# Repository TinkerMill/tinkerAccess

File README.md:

# tinkerAccess
The tinkerAccess system is a Raspberry Pi based access control system that can be used to prevent unauthorized users from using devices that require special training. It could also conceivably be used to control electronic lock boxes or doors.

The system was originally designed and created by Matt Stallard, Ron Thomas, and Matt Peopping for TinkerMill a makerspace in Longmont, CO. It is continually being maintained and enhanced by other contributors in the community.

### Install the tinkerAccess system

There are two main components to the system. If you intend to use the client and server software on separate physical devices, then you will want to review the individual documents regarding the installation, configuration, and operation of each respective piece.

- [tinker-access-server](/tinker_access_server/README.md) 
- [tinker-access-client](/tinker_access_client/README.md)

If however, you intend to use both the server and client on the same physical device, then you can follow these simple instructions. You will need to complete these client [prerequisites](/tinker_access_client/docs/prerequisites.md) before running the install script. 

From the Pi terminal:

```
git clone https://github.com/TinkerMill/tinkerAccess.git
cd tinkerAccess
sudo bash install.sh
```

After running the installation script, the configuration files for both the server and client are created, but they need to be modified for a proper setup, before rebooting or restarting the services to take effect.

Edit the server configuration file:

```
sudo nano /opt/tinkeraccess/server.cfg
```

Edit the client configuration file:

```
sudo nano /etc/tinker-access-client.conf
```

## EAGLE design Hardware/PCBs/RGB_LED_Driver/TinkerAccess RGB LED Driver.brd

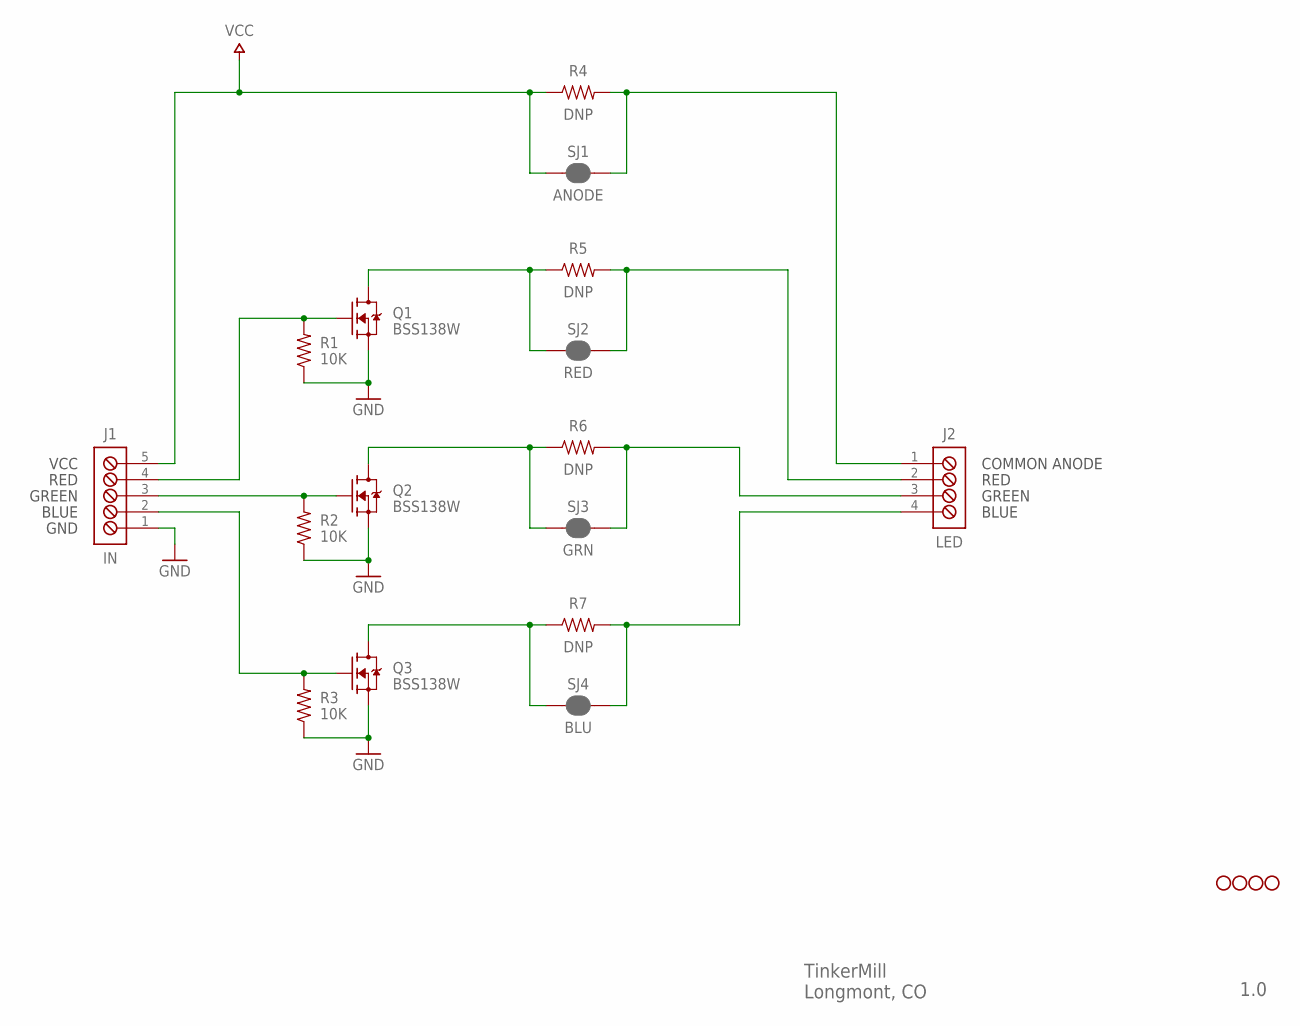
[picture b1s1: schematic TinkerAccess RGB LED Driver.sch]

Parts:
J1: IN; ON_SHORE_OSTVN05A150
J2: LED; ON_SHORE_OSTVN04A150
Q1, Q2, Q3: BSS138W; SOT323
R1, R2, R3: 10K; 0603
R4, R5, R6, R7: DNP; 0603
SJ1: ANODE; JMP_PAD_2X1_CLOSED_BY_PASTE
SJ2: RED; JMP_PAD_2X1_CLOSED_BY_PASTE
SJ3: GRN; JMP_PAD_2X1_CLOSED_BY_PASTE
SJ4: BLU; JMP_PAD_2X1_CLOSED_BY_PASTE
STANDOFF1, STANDOFF2, STANDOFF3, STANDOFF4: STANDOFF_2.3MM_NO_CU

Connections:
GND: J1.1, Q1.2 (S), Q2.2 (S), Q3.2 (S), R1.1, R2.1, R3.1
unnamed: J1.4, Q1.1 (G), R1.2
unnamed: J1.3, Q2.1 (G), R2.2
unnamed: J1.2, Q3.1 (G), R3.2
unnamed: J2.2, R5.2, SJ2.2
unnamed: J2.3, R6.2, SJ3.2
unnamed: J2.4, R7.2, SJ4.2
unnamed: Q1.3 (D), R5.1, SJ2.1
unnamed: Q2.3 (D), R6.1, SJ3.1
unnamed: Q3.3 (D), R7.1, SJ4.1
unnamed: J2.1, R4.2, SJ1.2
VCC: J1.5, R4.1, SJ1.1

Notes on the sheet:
VCC
RED
GREEN
BLUE
GND
COMMON ANODE
TinkerMill Longmont, CO
1.0

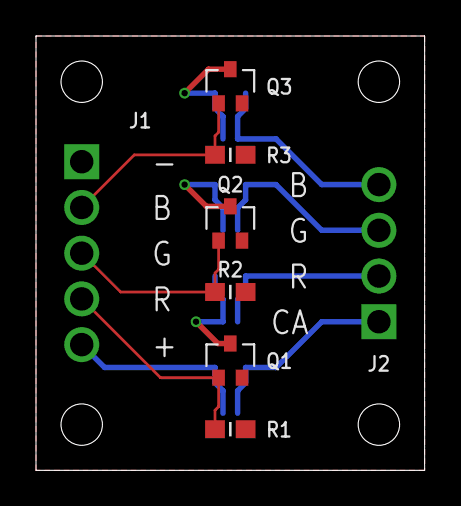
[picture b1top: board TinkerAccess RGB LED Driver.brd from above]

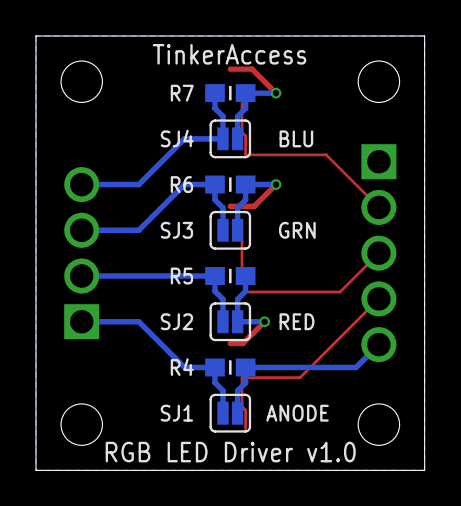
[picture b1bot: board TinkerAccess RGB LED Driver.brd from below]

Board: 2 copper layers, 21.6 x 24.1 mm, 20 parts (8 on the bottom side), 12 nets.

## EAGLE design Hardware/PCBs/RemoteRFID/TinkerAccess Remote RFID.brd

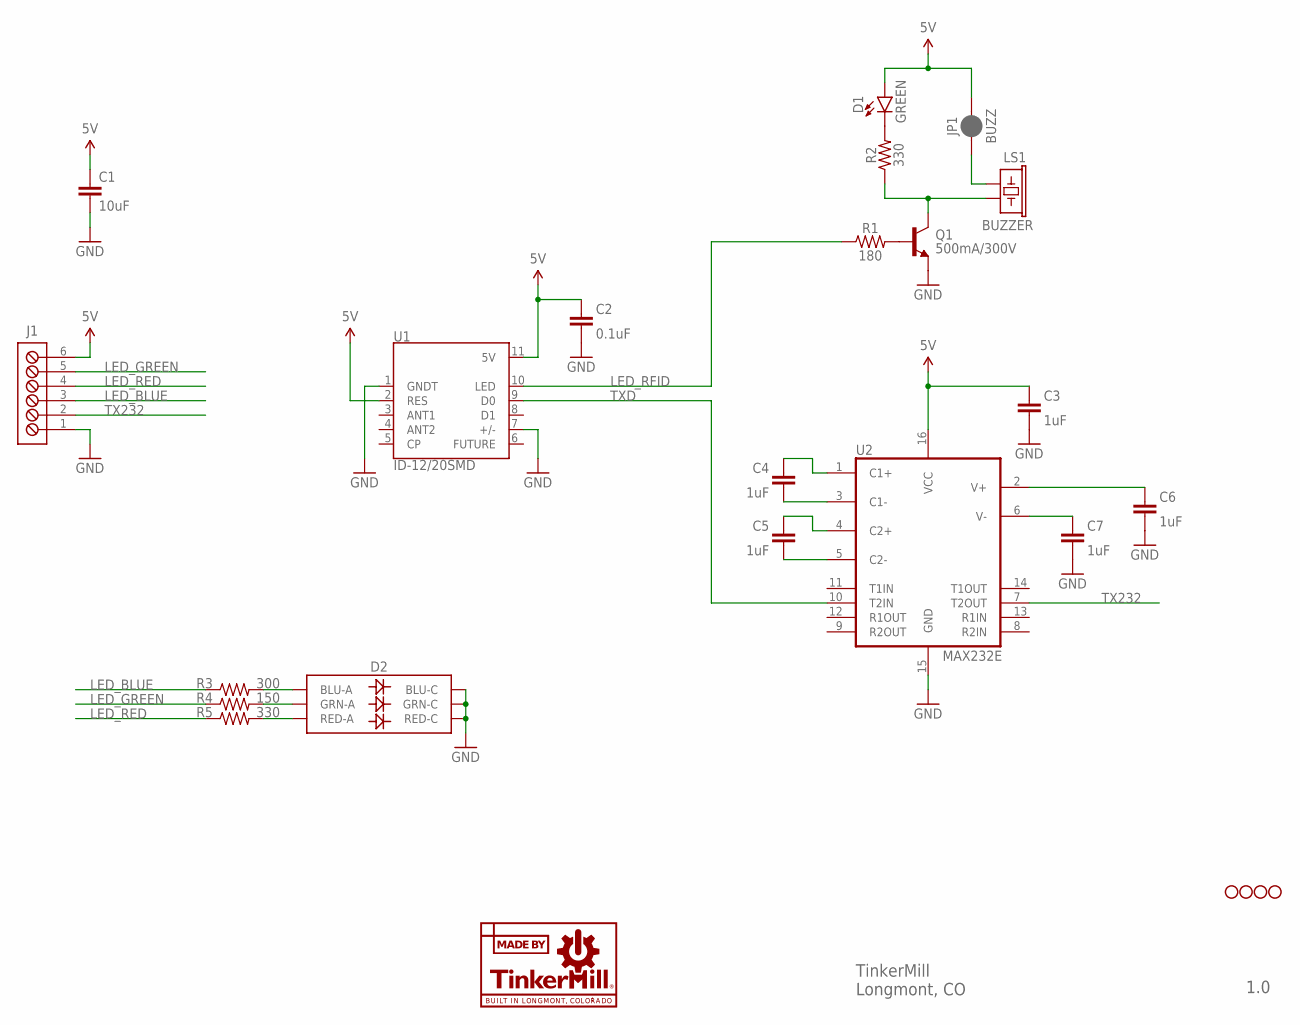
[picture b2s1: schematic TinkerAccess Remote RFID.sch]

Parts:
C1: 10uF; 1206
C2: 0.1uF; 0603
C3, C4, C5, C6, C7: 1uF; 0603
D1: GREEN; LED-1206
D2: LED-RGBNO_IC; LED-TRICOLOR-5050
J1: TB_6X1_TE_CONN_ED555_6DS; TE_CONN_ED555_6DS
JP1: BUZZ; SMT-JUMPER_2_NC_PASTE_NO-SILK
LOGO1: MADE_BY_TINKERMILL
LS1: BUZZER; BUZZER-CCV
Q1: 500mA/300V; SOT23-3
R1: 180; 0603
R2, R5: 330; 0603
R3: 300; 0603
R4: 150; 0603
STANDOFF1, STANDOFF2, STANDOFF3, STANDOFF4: STANDOFF_3.2MM_NO_CU_MASK
U1: ID-12/20SMD; ID-12_SMD
U2: MAX232E; TSSOP16

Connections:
5V: C1.1, C2.2, C3.2, D1.A, J1.6, JP1.2, U1.2 (RES), U1.11 (5V), U2.16 (VCC)
GND: C1.2, C2.1, C3.1, C6.1, C7.1, D2.4 (BLU-C), D2.5 (RED-C), D2.6 (GRN-C), J1.1, Q1.2 (E), U1.1 (GNDT), U1.7 (+/-), U2.15 (GND)
LED_BLUE: J1.3, R3.1
LED_GREEN: J1.5, R4.1
LED_RED: J1.4, R5.1
LED_RFID: R1.1, U1.10 (LED)
unnamed: Q1.1 (B), R1.2
unnamed: JP1.1, LS1.+ (1)
unnamed: LS1.- (2), Q1.3 (C), R2.1
unnamed: D1.C, R2.2
unnamed: C4.1, U2.3 (C1-)
unnamed: C4.2, U2.1 (C1+)
unnamed: C5.1, U2.5 (C2-)
unnamed: C5.2, U2.4 (C2+)
unnamed: D2.2 (RED-A), R5.2
unnamed: D2.1 (GRN-A), R4.2
unnamed: D2.3 (BLU-A), R3.2
unnamed: C6.2, U2.2 (V+)
unnamed: C7.2, U2.6 (V-)
TX232: J1.2, U2.7 (T2OUT)
TXD: U1.9 (D0), U2.10 (T2IN)

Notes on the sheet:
TinkerMill Longmont, CO
1.0

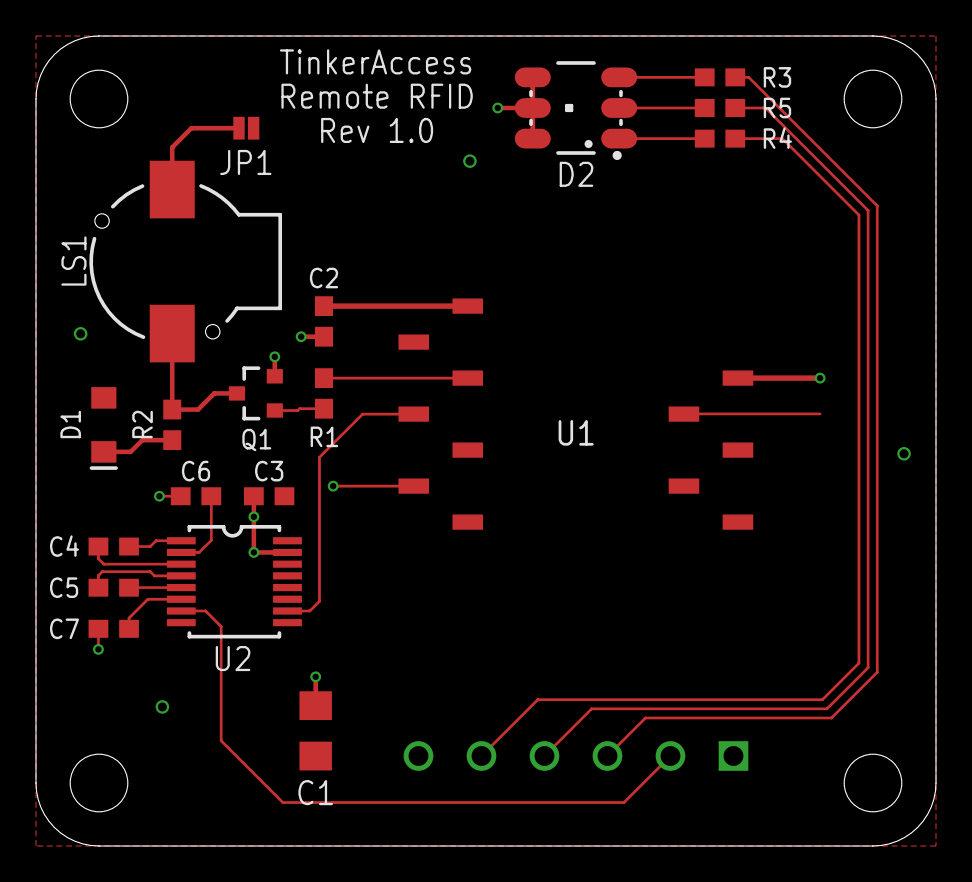
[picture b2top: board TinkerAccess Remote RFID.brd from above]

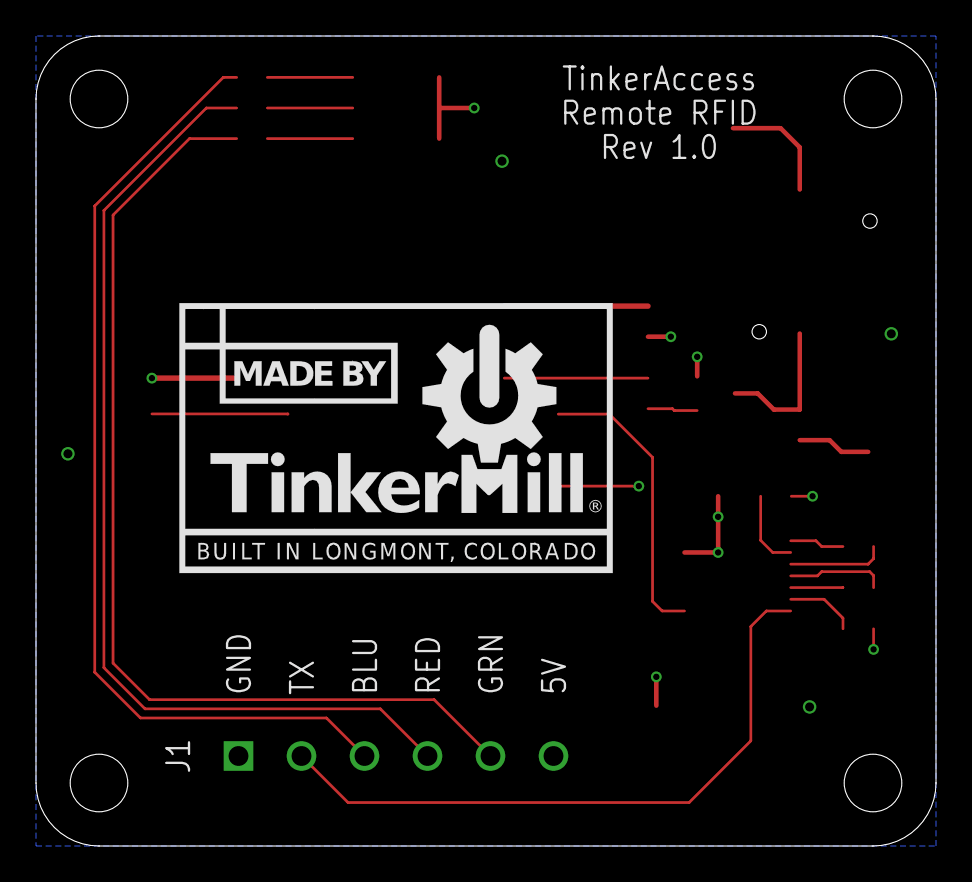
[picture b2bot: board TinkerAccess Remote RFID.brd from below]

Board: 2 copper layers, 50.0 x 45.0 mm, 25 parts (2 on the bottom side), 21 nets.

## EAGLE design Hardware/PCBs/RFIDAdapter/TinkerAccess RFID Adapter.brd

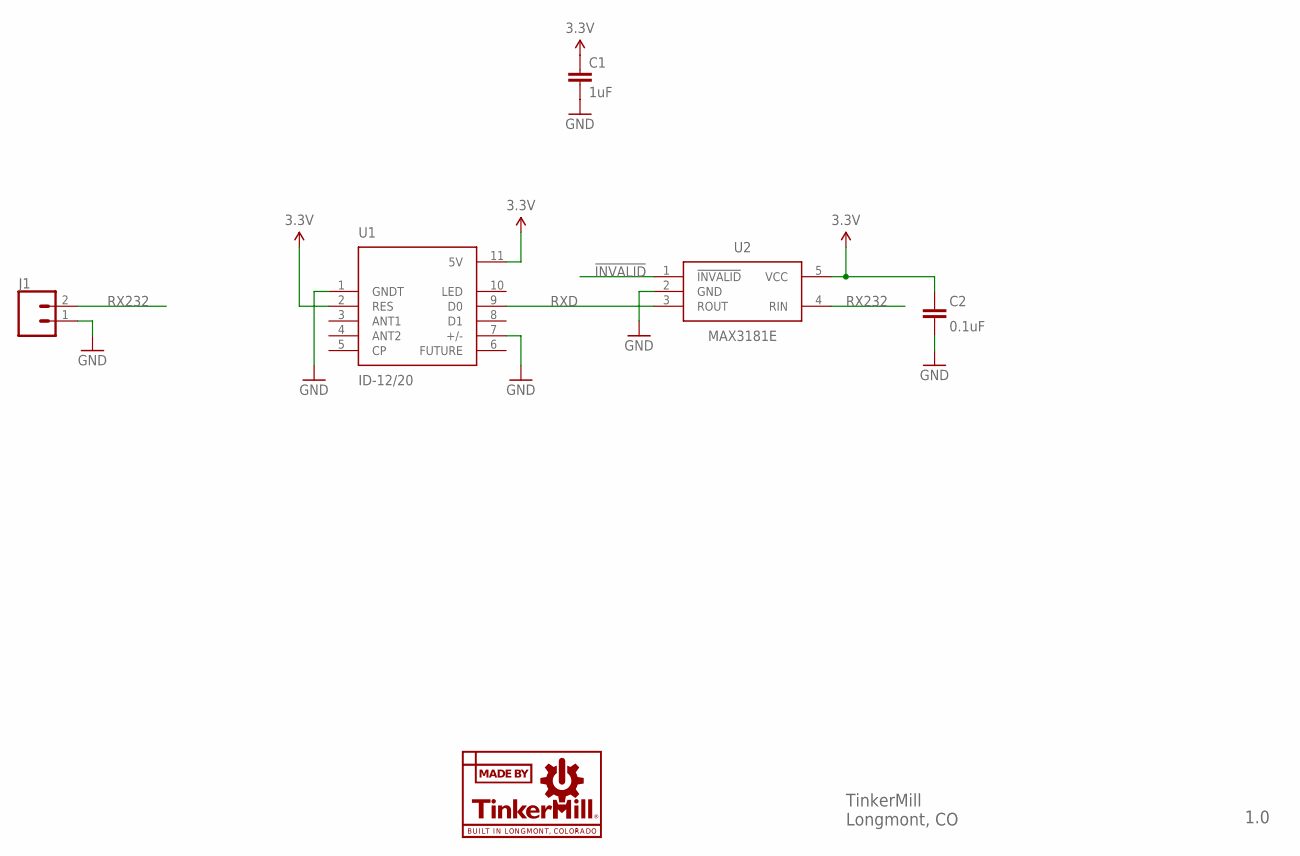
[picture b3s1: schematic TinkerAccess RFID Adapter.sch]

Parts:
C1: 1uF; 0603
C2: 0.1uF; 0603
J1: CONN_025MM; SCREWTERMINAL-5MM-2
LOGO1: MADE_BY_TINKERMILL
U1: ID-12/20; ID-12
U2: MAX3181E; SOT23-5

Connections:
3.3V: C1.1, C2.2, U1.2 (RES), U1.11 (5V), U2.5 (VCC)
!INVALID: U2.1 (!INVALID)
GND: C1.2, C2.1, J1.1, U1.1 (GNDT), U1.7 (+/-), U2.2 (GND)
RX232: J1.2, U2.4 (RIN)
RXD: U1.9 (D0), U2.3 (ROUT)

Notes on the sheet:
TinkerMill Longmont, CO
1.0

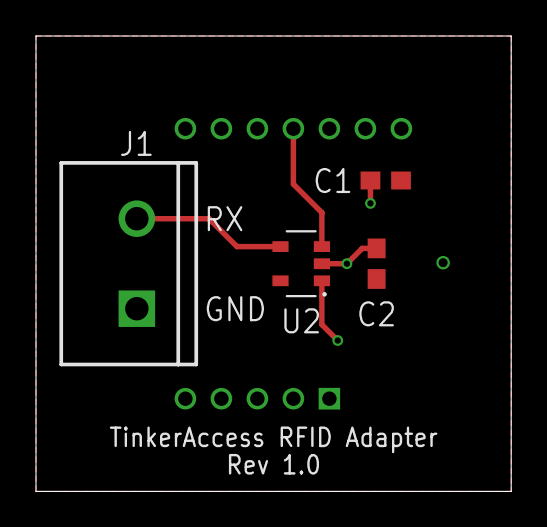
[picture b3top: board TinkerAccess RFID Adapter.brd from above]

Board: 2 copper layers, 26.4 x 25.3 mm, 6 parts (1 on the bottom side), 4 nets.

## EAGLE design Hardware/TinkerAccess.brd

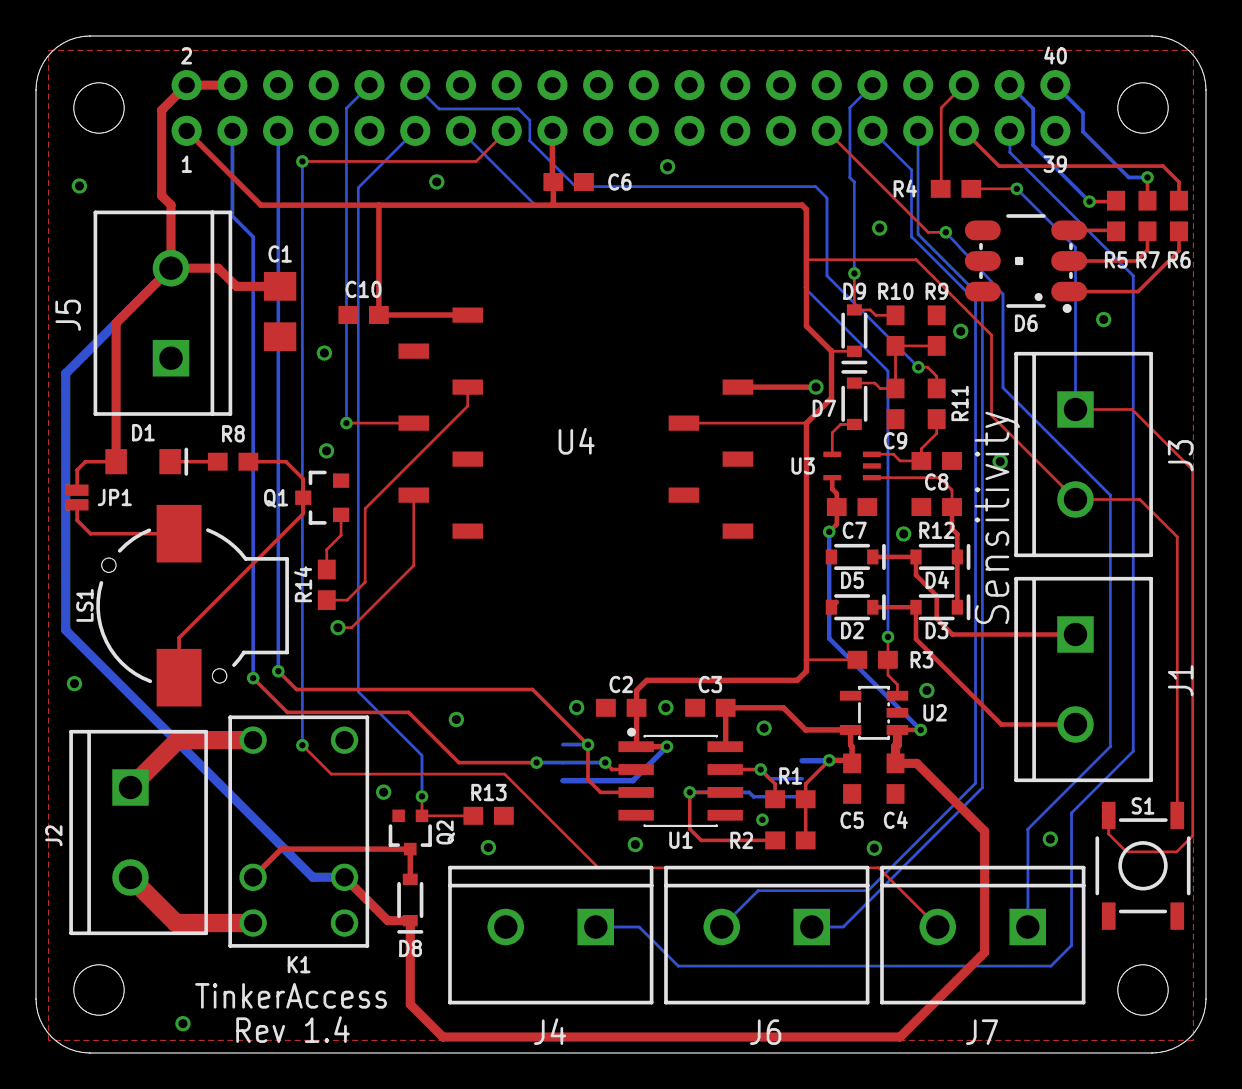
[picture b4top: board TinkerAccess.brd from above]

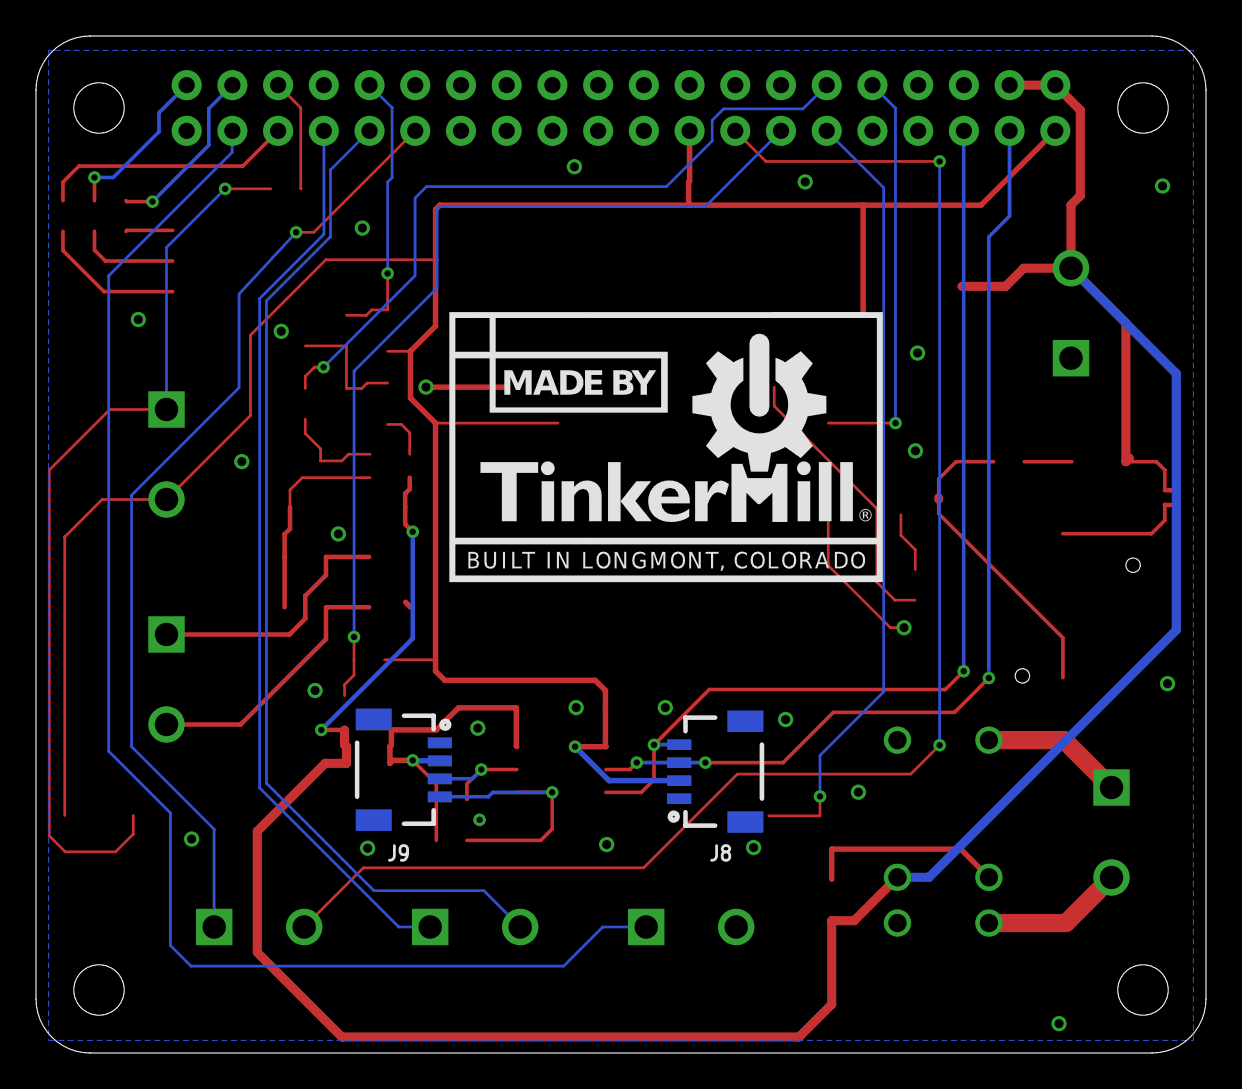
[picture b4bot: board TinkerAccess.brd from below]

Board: 2 copper layers, 65.0 x 56.5 mm, 54 parts (3 on the bottom side), 40 nets.

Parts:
C1: 10uF; 1206
C2, C3, C7, C10: 0.1uF; 0603
C4, C5, C6, C8, C9: 1uF; 0603
D1: GREEN; LED-1206
D2, D3, D4, D5, D7, D8, D9: 1A/100V; SOD-323
D6: LED-TRICOLOR-5050
J1, J2, J3, J4, J5, J6, J7: SCREWTERMINAL-5MM-2
J8, J9: 1X04_1MM_RA
JP1: BUZZ; SMT-JUMPER_2_NC_PASTE_NO-SILK
K1: RELAY-SPDT-2-G5V; RELAY-G5V
LOGO1: MADE_BY_TINKERMILL
LS1: BUZZER; BUZZER-CCV
Q1: 500mA/300V; SOT23-3
Q2: 310mA/60V/1.6Ω; SOT323
R1, R2, R3, R4, R11, R13: 10k; 0603
R5: 300; 0603
R6: 150; 0603
R7, R8: 330; 0603
R9: 100k; 0603
R10, R12: 1k; 0603
R14: 180; 0603
RPI1: RASPBERRYPI_BPLUS_HATNOSLOTS; PI_HAT_NOSLOTS
S1: LogOut; TACTILE_SWITCH_SMD_5.2MM
U1: Si8600AC; SOIC127P600X175-8
U2: AP2112; SOT23-5
U3: ADCMP-371; SC-70-5
U4: ID-12/20SMD; ID-12_SMD

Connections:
3.3V: C2.2, C6.1, C10.2, D9.C, J3.2, J8.2, R3.1, RPI1.1, RPI1.17, S1.1, U1.1, U4.2, U4.11
3.3V_EN: R3.2, RPI1.13, U2.3
5V: C1.1, C4.1, C7.1, D1.A, D8.C, J5.2, JP1.2, K1.2, RPI1.2, RPI1.4, U2.1, U3.5
+3V3: C3.2, C5.1, J9.2, R1.1, R2.1, U1.8, U2.5
AC1: D4.A, D5.C, J1.1
AC2: D2.C, D3.A, J1.2
BSCL: J9.4, R2.2, U1.6
BSDA: J9.3, R1.2, U1.7
COMPOUT: D7.A, U3.4
DETECT: C9.1, D7.C, R9.1, R10.1
GND: C1.2, C2.1, C3.1, C4.2, C5.2, C6.2, C7.2, C8.2, C9.2, C10.1, D2.A, D5.A, D6.4, D6.5, D6.6, J4.2, J5.1, J8.1, J9.1, Q1.2, Q2.2, R9.2, R12.1, R13.2, RPI1.6, RPI1.9, RPI1.14, RPI1.20, RPI1.25, RPI1.30, RPI1.34, RPI1.39, U1.4, U1.5, U2.2, U3.2, U4.1, U4.7
GPIO5: J7.1, RPI1.29
GPIO6: J6.2, RPI1.31
GPIO12: D9.A, R10.2, RPI1.32
GPIO13: J6.1, RPI1.33
GPIO16: R4.2, RPI1.36
GPIO18: R11.1, RPI1.12
GPIO22: J7.2, RPI1.15
GPIO26: J4.1, RPI1.37
LED_BLUE: R5.1, RPI1.38
LED_GREEN: R6.1, RPI1.35
LED_RED: R7.1, RPI1.40
LED_RFID: R14.1, U4.10
LOGOUT: J3.1, R4.1, S1.3
unnamed: Q1.1, R14.2
unnamed: JP1.1, LS1.+
unnamed: LS1.-, Q1.3, R8.1
unnamed: D1.C, R8.2
unnamed: D8.A, K1.9, Q2.3
unnamed: J2.1, K1.6
unnamed: J2.2, K1.10
unnamed: D6.2, R7.2
unnamed: D6.1, R6.2
unnamed: D6.3, R5.2
RECT+: D3.C, D4.C, R12.2, U3.1
RELAY: Q2.1, R13.1, RPI1.11
RXD: RPI1.10, U4.9
SCL: J8.4, RPI1.5, U1.3
SDA: J8.3, RPI1.3, U1.2
VREF: C8.1, R11.2, U3.3

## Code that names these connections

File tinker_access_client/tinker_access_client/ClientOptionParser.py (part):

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ClientOptionDefaults = {
    ClientOption.DEBUG: False,
    ClientOption.LOG_LEVEL: 40,
    ClientOption.PIN_LOGOUT: 16,
    ClientOption.PIN_LED_RED: 21,
    ClientOption.DEVICE_ID: None,
    ClientOption.PIN_LED_BLUE: 20,
    ClientOption.REBOOT_DELAY: 300,
    ClientOption.PIN_LED_GREEN: 19,
    ClientOption.AUTO_UPDATE: False,
    ClientOption.FORCE_UPDATE: False,
    ClientOption.PIN_POWER_RELAY: 17,
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        )

        self.__parser.add_option(
            '--pin-logout',
            help='the logout pin [default:%default]',
            default=ClientOptionDefaults[ClientOption.PIN_LOGOUT],
            dest=ClientOption.PIN_LOGOUT,
            type='int',
            action='store'
        )

        self.__parser.add_option(
            '--pin-power-relay',
            help='the power relay pin [default:%default]',
            default=ClientOptionDefaults[ClientOption.PIN_POWER_RELAY],
            dest=ClientOption.PIN_POWER_RELAY,
            type='int',
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        self.__parser.add_option(
            '--pin-led-red',
            help='the red led pin [default:%default]',
            default=ClientOptionDefaults[ClientOption.PIN_LED_RED],
            dest=ClientOption.PIN_LED_RED,
            type='int',
            action='store'
        )
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        self.__parser.add_option(
            '--pin-led-green',
            help='the green led pin [default:%default]',
            default=ClientOptionDefaults[ClientOption.PIN_LED_GREEN],
            dest=ClientOption.PIN_LED_GREEN,
            type='int',
            action='store'
        )
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        self.__parser.add_option(
            '--pin-led-blue',
            help='the blue led pin [default:%default]',
            default=ClientOptionDefaults[ClientOption.PIN_LED_BLUE],
            dest=ClientOption.PIN_LED_BLUE,
            type='int',
            action='store'
        )
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        )

        self.__parser.add_option(
            '--pin-bypass-detect',
            help='the bypass detect pin [default:%default]',
            default=ClientOptionDefaults[ClientOption.PIN_BYPASS_DETECT],
            dest=ClientOption.PIN_BYPASS_DETECT,
            type='int',
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
        self.__parser.add_option(
            '--use-estop',
            help='use the e-stop pin to detect an e-stop event [default:%default]',
            default=ClientOptionDefaults[ClientOption.USE_ESTOP],
            dest=ClientOption.USE_ESTOP,
            action='store_true'
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
        self.__parser.add_option(
            '--use-bypass-detect',
            help='use the bypass detect pin function [default:\'%default\']',
            default=ClientOptionDefaults[ClientOption.USE_BYPASS_DETECT],
            dest=ClientOption.USE_BYPASS_DETECT,
            action='store_true'
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
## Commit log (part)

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2015-07-12 initial scanner
2015-08-16 dd ser
2015-09-02 more html changes
2015-09-02 adding ignore file
2015-09-23 inst
2015-09-30 New user table and web interface to use it
2015-10-29 fix testing instruction
2015-10-29 Mostly working server code, you can add and remove access for users
2015-10-29 updated docs
2015-10-29 fix servername
2015-10-29 fix formatting
2015-10-30 install script and startup scripts
2015-10-30 fixing installer
2015-10-30 point to database
2015-10-30 working
2015-10-31 add python deps to installer
2015-11-04 initial checkin
2015-11-04 Changed return value in memberAccessServer.py. We actually will not need this memberAccessServer.py file. It was only used during early development testing to confirm flask was working correctly.
2015-11-05 don't add to new users over and over, only add if they are not in new users and if they are not in users
2015-11-13 Adding Secutiry somewhat
2015-11-18 Corrected issue involved with invalid user scanning while a valid user is logged in.
2015-11-18 changes for lcd 0x06 to 0x0C
2015-11-18 update docs
2015-11-18 full path in install
2015-11-18 updated startup script for tinkerclient
2015-11-19 bug deleting wrong user
2015-11-19 move sql up
2015-11-19 redirect to login if you are not logged in
2015-11-19 change perms 755 badge scan
2016-01-21 test2
    testing webhook2
2016-01-23 push to slack
2016-01-23 add user to message
2016-01-23 simple test script
2016-01-23 added LED status
2016-01-23 fix template error
2016-01-23 fixing template for log
2016-01-27 client files into oldcode
2016-01-30 mostly working
2016-01-31 logging?
2016-01-31 cleanup file names
2016-01-31 device manager added back
2016-01-31 python header
2016-01-31 make image smaller
2016-02-12 gave server static ip
2016-02-12 removed old instructions.
2016-02-28 Fixed pin_current_sense technology
2016-02-28 move led function up
2016-02-29 more verbose go the F away message
2016-02-29 2 f'in seconds... happy matt?
2016-03-04 Added coast-down delay functionality
    If a logout request happens while the machine is running, this added
    functionality ensures that the logout event doesn't execute until a
    coast-down period elapses.
2016-03-06 changed load resistor value
2016-03-07 RFID diagram - Unscrewing the screw up
2016-03-07 Created docs folder
2016-03-13 This closes #3, and closes #4
2016-03-13 more errors
2016-03-13 fix typo
2016-03-13 time input wrong.corrected
2016-03-13 Verbose output on machine down, and global for currentBadge
2016-03-13 startup script installs new client
2016-04-15 remove continue
2016-04-20 fixing matts vars
2016-05-09 updated docs and install script
2016-05-11 adding run.cfg back
2016-05-11 updated true=0 false=1 for those that are overly anal about their trues and falses
2016-05-11 Mario mode added to client, hold down logout for 2 seconds to activate click logout again to logout
2016-05-13 remove server debug line
2016-05-15 lowered count cycle on reset button hold down
    went from 2000 to 20 since there is a .1 sleep cycle each time it loops... so I only have to hold down for 2 second instead of 200 :)
2016-05-16 Update client.py
    fixy fixy
2016-05-16 more error checking
2016-05-16 keep mario message up, continue if can't talk to server
2016-05-16 option to force an update from script
2016-05-16 place abs path back into server config for db
2016-05-17 lalalalal
2016-05-17 log to syslog on client
2016-05-20 Capture entire 12-character RFID badge number.
2016-05-26 clean old records on new user
2016-05-26 flush serial after reading data
2016-05-26 read 12 prev chars
2016-05-27 lalala server fix
2016-05-28 Corrected Service Management Instructions
2016-05-31 Upload CSV option on server
2016-07-06 Uploaded RFIDTagRegster.py.
    RFIDTagRegister.py is a script that reads in an RFID tag number using the Sparkfun RFID reader and auto-types the tag number.
2016-11-02 Updated circuit schematics
    Improved current sense circuit and corrected LED resistor values.
2016-11-09 Fixed typo and clarified variables
2016-11-09 Missed a tab/space... Oops!
2016-11-09 Use modulo for minutes remaining.
2016-11-12 Fixed arithmetic to display h:m:s on LCD
2016-11-12 h:m:s arithmetic correction number 2, I swear I know math...
2016-11-12 Importing math
2016-11-13 Added 2 second timeout for server requests
2016-11-13 Added 2 second delay after error logging in message display
2016-11-23 Increased server response timeout to five seconds.
2016-11-29 Refactor to add logging for all client request
2016-11-30 Revert "Removed code that would cause duplicate log messages"
    This reverts commit 1f643b83fb6d0a186454d6c3408f051573ecaa93.
2016-12-22 Increased timeout to 10 seconds.
2017-03-17 Set build VERSION number
2017-04-02 (issue): #11 - Current Sense/Coastdown Time not implemented correctly
2017-05-09 Convert LCD from GPIO to I2C.
2017-05-11 Change smbus to smbus2, add smbus2 to setup.py
2017-05-11 Remove .GPIO from __write_to_lcd
2017-05-11 Update DeviceApi to match LcdApi
2017-05-11 Update VirtualDevice in integration test utils to match DeviceApi
2017-05-12 Add 0 to write_byte_data invocation.
2017-05-12 Remove __write_to_lcd from VirtualDevice.py
2017-05-13 Break i2c_device class into its own file
2017-05-18 Add fritzing file and exported images
2017-05-18 Update client prerequisite documentation
2017-07-12 Add new Fritzing file for Raspberry Pi Hat design
2017-07-12 Add Hat board exports
2017-07-18 Add power to U2 LM393 thanks to Tyler
2017-07-19 Fix issues found by Tyler Dow and Don Vukovic
2017-07-19 Update exported Bill of Materials and Netlists
2017-07-19 Update exported PCB files
2019-04-09 Update Client.py
    We are opening the file but never closing it. Should always close a file when done with it...
2019-06-26 basic tool summary page
2019-08-27 tool summary updates
2019-12-19 Create TinkerAccess.brd
    Version V1_2 from Don Vukovic
2019-12-20 Create LICENSE
2020-02-18 Fixed Consistancy Errors
    After fixing consistancy errors I now need to make the repairs to the pad designs.
2020-02-20 Finshied Removing HW bugs
    Fixed missing trace, Pad sizes for ADCMP371 and SI8600. Also added a trace for the 3.3V en to a GPIO for restarting the
2020-02-23 bugfix to get correct PID to kill on shutdown
    Running `/opt/tinkeraccess/server.py` directly saves the wrong PID in
    `/var/run/tinkerAccessServer.pid`, which is later used to kill the
    server when the service is stopped. Instead, running the server via
    `python /opt/tinkeraccess/server.py` reports the correct PID.
2020-02-26 Added --noreload option to server
    Prevents zombie server when run from /etc/init.d/tinkerserver. The Flask
    server by default runs a child process, which is the actual webserver,
    so that the parent can monitor the server files and restart the child
    when they change. This, however, interferes with start-stop-daemon's
    ability to stop the server. This change fixes that behavior.
2020-05-23 TinkerBoard Update
    Fixed Drill Hole size to match Design rules.
    Fixed Pad sizes.
    Fixed AirWires.
2020-05-24 added pulldown
    Added pulldown resistor to 3v3 Enable line
2020-05-29 Cleaned up schematic notes
2020-06-19 Updates to machine shop TA schematic.
2020-06-20 ran 2to3
2020-06-27 Added support for new SparkFun LCD-14072 SerLCD display Added support for an E-STOP input pin to detect an event and automatically logout the current user Added support for the 3.3V enable pin added 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
2020-06-27 Moved E-Stop input to GPIO6 Added machine shop faceplate DXF file
2020-06-27 Fixed test assertions for training mode
2020-06-28 Added example client config file
2020-07-07 Added a bypass/tamper detect input
2020-07-14 Updated machine shop schematic with bypass detect changes
2020-08-05 prototype of image capture/posting
2020-08-06 moved server.cfg to example_server.cfg
2020-08-14 Cleaned up the tests so that they will pass with recent code changes
2020-08-14 Added alarm beacon wiring to machine shop TinkerAccess schematic
2020-08-14 fixes to run without webcam
2020-08-19 Documentation and install script updates for the client.
2020-08-20 Changes for PCB spin with a PWM based current sense detect setting
2020-08-20 Documentation updates for programmable current detection tuning
2020-08-20 Fix documentation typos
2020-09-08 Changes for v1.4 of TinkerAccess PCB
2020-11-02 Added remote RFID PCBs
2020-11-09 door handling
2020-12-01 Updated client configuration documentation
2020-12-02 Fixed bug with new 'use_pgm_current_threshold' config option. Added RGB LED Driver PCB.
2020-12-06 Updated client with changes to support doors.
2020-12-06 Changes to server to support device authentication to all users in the database
2021-02-20 Updated the device configuration files
2021-04-21 Added Shopbot schematics, added PCB BOMs, and updated machine shop schematics
2021-05-04 For all updated nodes, updated config files to change reboot on error time from 300 minutes to 5 minutes. Added schematic and BOM for laser cutter implementation.
2021-05-10 Updated front door client version and modified config file so unlock time is between 7:30am & 6pm.
2021-06-06 Fixed some documentation errors, added faceplate dxf files.
2021-06-24 Added documentation for table saw implementation
2021-07-01 Added schematic and documentation for jointer/planer and wood lathe upgrades. Added datasheets for woodshop door parts.
2021-09-24 Fix a bug on the server, where the server was not responding to clients when the internet was down because the Slack hook connection failed.
2021-12-01 Added schematic and documentation for pottery door.
2022-08-02 Added a feature where users can be deactivated instead of deleting. Also added timed access to devices and ability to lockout for maintenance. Also added 24hr access option to users to override devic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
2022-08-03 Improve unlock times for doors.
2022-08-07 Added script to deactivate all users
2023-01-14 Added W Bay Door documentation
2023-02-19 only send Slack notifications for time-limited devices (i.e. not doors)
2023-06-01 Added Powermatic Bandsaw documentation
2023-06-15 Swapped around monochrome and RGB LCD displays between doors and machines. Updated BOM and config files to reflect these changes.
2024-03-14 Cleaned up PCB BOMs. Added JLCPCB part numbers.
2024-12-23 BUGFIX: deviceUsageSummary will now work in december. TESTING: Added unit tests for ToolSummaryInterface for bugfix TESTING: Added Hurl tests for most (all?) API endpoints, along with test data CLEAN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
2024-12-23 Bump jinja2 from 2.11.3 to 3.1.4 in /tests
    Bumps [jinja2](https://github.com/pallets/jinja) from 2.11.3 to 3.1.4.
    - [Release notes](https://github.com/pallets/jinja/releases)
    - [Changelog](https://github.com/pallets/jinja/blob/main/CHANGES.rst)
    - [Commits](https://github.com/pallets/jinja/compare/2.11.3...3.1.4)
    ---
    updated-dependencies:
2024-12-23 Bump jinja2 from 2.11.3 to 3.1.5 in /tests
    Bumps [jinja2](https://github.com/pallets/jinja) from 2.11.3 to 3.1.5.
    - [Release notes](https://github.com/pallets/jinja/releases)
    - [Changelog](https://github.com/pallets/jinja/blob/main/CHANGES.rst)
    - [Commits](https://github.com/pallets/jinja/compare/2.11.3...3.1.5)
    ---
    updated-dependencies:
2025-03-05 Bump jinja2 from 2.11.3 to 3.1.6 in /tests
    Bumps [jinja2](https://github.com/pallets/jinja) from 2.11.3 to 3.1.6.
    - [Release notes](https://github.com/pallets/jinja/releases)
    - [Changelog](https://github.com/pallets/jinja/blob/main/CHANGES.rst)
    - [Commits](https://github.com/pallets/jinja/compare/2.11.3...3.1.6)
    ---
    updated-dependencies:
2025-10-15 Rust work
2025-10-16 Remove extra <td> from ShowUsers
2025-11-19 WIP: Initial rust commit
2026-02-10 adding cargo generated files and build files to gitignore
2026-02-16 WIP: checkpoint before requested changes
2026-02-16 Add single test for printing JSON for getStateCmd and add camelCase conversion
2026-02-17 WIP: Add Message for WebSocket exchanges with TA ESP32 Nodes
2026-02-20 updating .gitignore to keep build/lock files from being committed
2026-02-22 Adding in new documentation files to make it easier to compare the AC APIs for the old and new implementation, adding in a log that happens every time the server gets a BadCmd message
2026-02-25 removing cargo.lock from .gitignore, removing ssr dependency on tower, reverting device.rs and adding nowarn macros to a few files for now
2026-02-25 cleaning up last warning for now
2026-05-20 Tell dist to ignore the extra permission we had to add to the github workflow

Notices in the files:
parts and their libraries:
SparkFun-Connectors: Licensing: Creative Commons ShareAlike 4.0 International - https://creativecommons.org/licenses/by-sa/4.0
microbuilder: This work is placed in the public domain, and may be freely used for commercial and non-commercial work with the following conditions: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
